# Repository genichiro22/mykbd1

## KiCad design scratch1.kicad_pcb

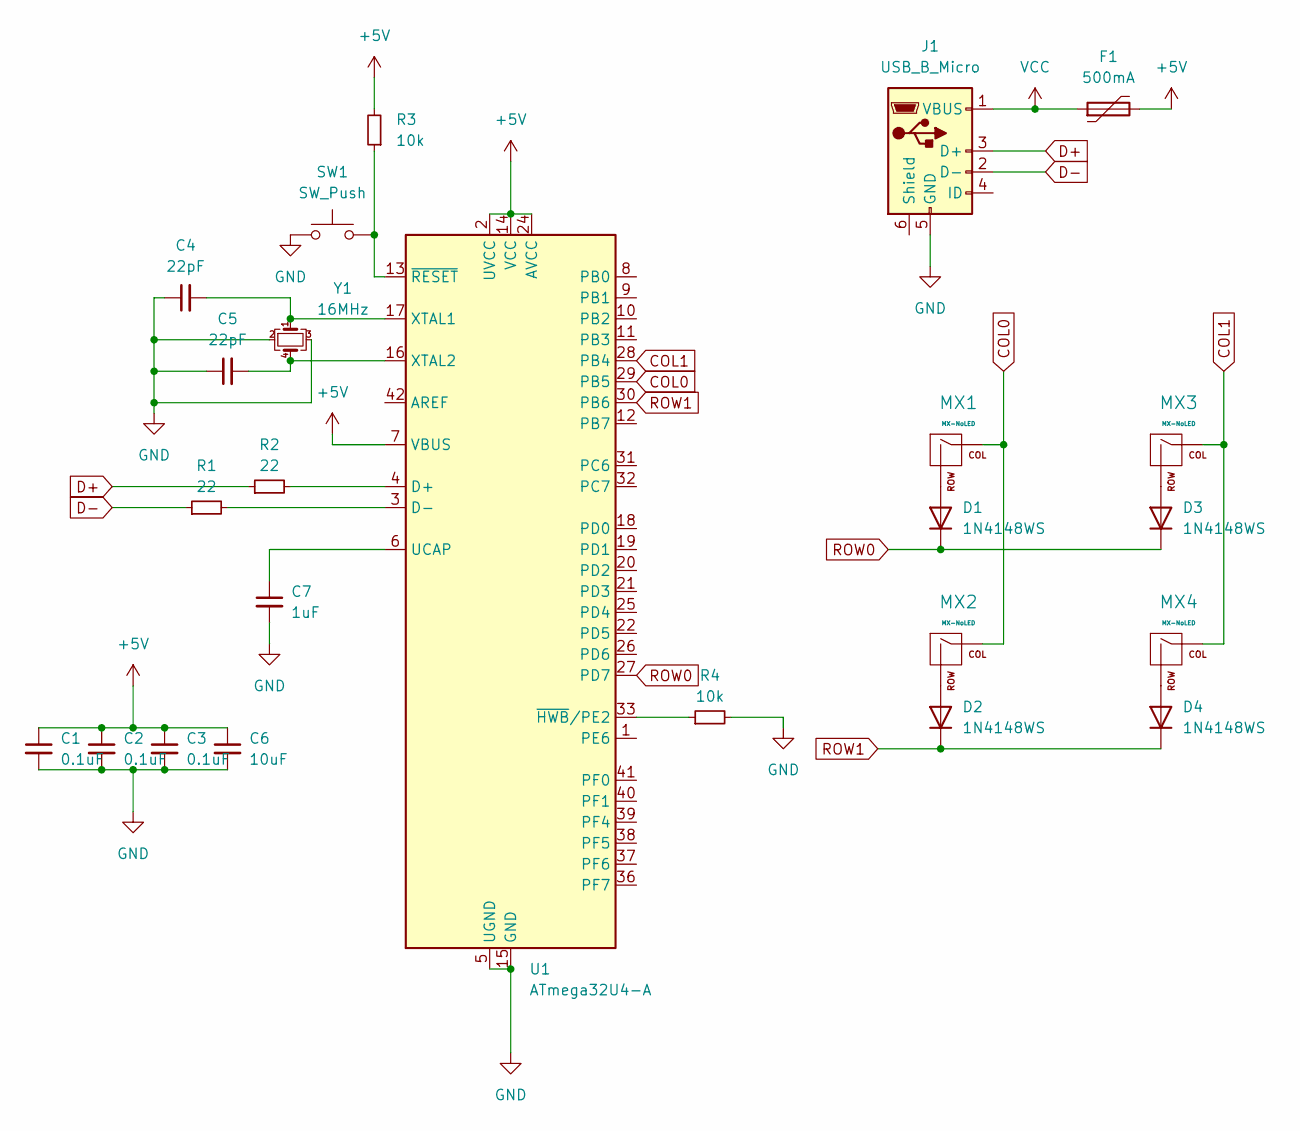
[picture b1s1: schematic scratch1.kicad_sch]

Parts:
C1, C2, C3: 0.1uF; C_0805_2012Metric
C4, C5: 22pF; C_0805_2012Metric
C6: 10uF; C_0805_2012Metric
C7: 1uF; C_0805_2012Metric
D1, D2, D3, D4: 1N4148WS; D_SOD-323
F1: 500mA; Fuse_1206_3216Metric
J1: USB_B_Micro; Molex-0548190589
MX1, MX2, MX3, MX4: MX-NoLED; MXOnly-1U-NoLED
R1, R2: 22; R_0805_2012Metric
R3, R4: 10k; R_0805_2012Metric
SW1: SW_Push; SKQG-1155865
U1: ATmega32U4-A; TQFP-44_10x10mm_P0.8mm
Y1: 16MHz; Crystal_SMD_3225-4Pin_3.2x2.5mm

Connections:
+5V: C1.1, C2.1, C3.1, C6.1, F1.2, R3.2, U1.2 (UVCC), U1.7 (VBUS), U1.14 (VCC), U1.24 (AVCC), U1.34 (VCC), U1.44 (AVCC)
COL0: MX1.1 (COL), MX2.1 (COL), U1.29 (PB5)
COL1: MX3.1 (COL), MX4.1 (COL), U1.28 (PB4)
D+: J1.3 (D+), R2.1
D-: J1.2 (D-), R1.1
GND: C1.2, C2.2, C3.2, C4.1, C5.1, C6.2, C7.2, J1.5 (GND), R4.2, SW1.1, U1.5 (UGND), U1.15 (GND), U1.23 (GND), U1.35 (GND), U1.43 (GND), Y1.2, Y1.3
unnamed: D1.2 (A), MX1.2 (ROW)
unnamed: D2.2 (A), MX2.2 (ROW)
unnamed: D3.2 (A), MX3.2 (ROW)
unnamed: D4.2 (A), MX4.2 (ROW)
unnamed: R2.2, U1.4 (D+)
unnamed: R1.2, U1.3 (D-)
unnamed: C7.1, U1.6 (UCAP)
unnamed: C4.2, U1.17 (XTAL1), Y1.1
unnamed: C5.2, U1.16 (XTAL2), Y1.4
unnamed: R4.1, U1.33 (~HWB/PE2)
unnamed: R3.1, SW1.2, U1.13 (~RESET)
ROW0: D1.1 (K), D3.1 (K), U1.27 (PD7)
ROW1: D2.1 (K), D4.1 (K), U1.30 (PB6)
VCC: F1.1, J1.1 (VBUS)

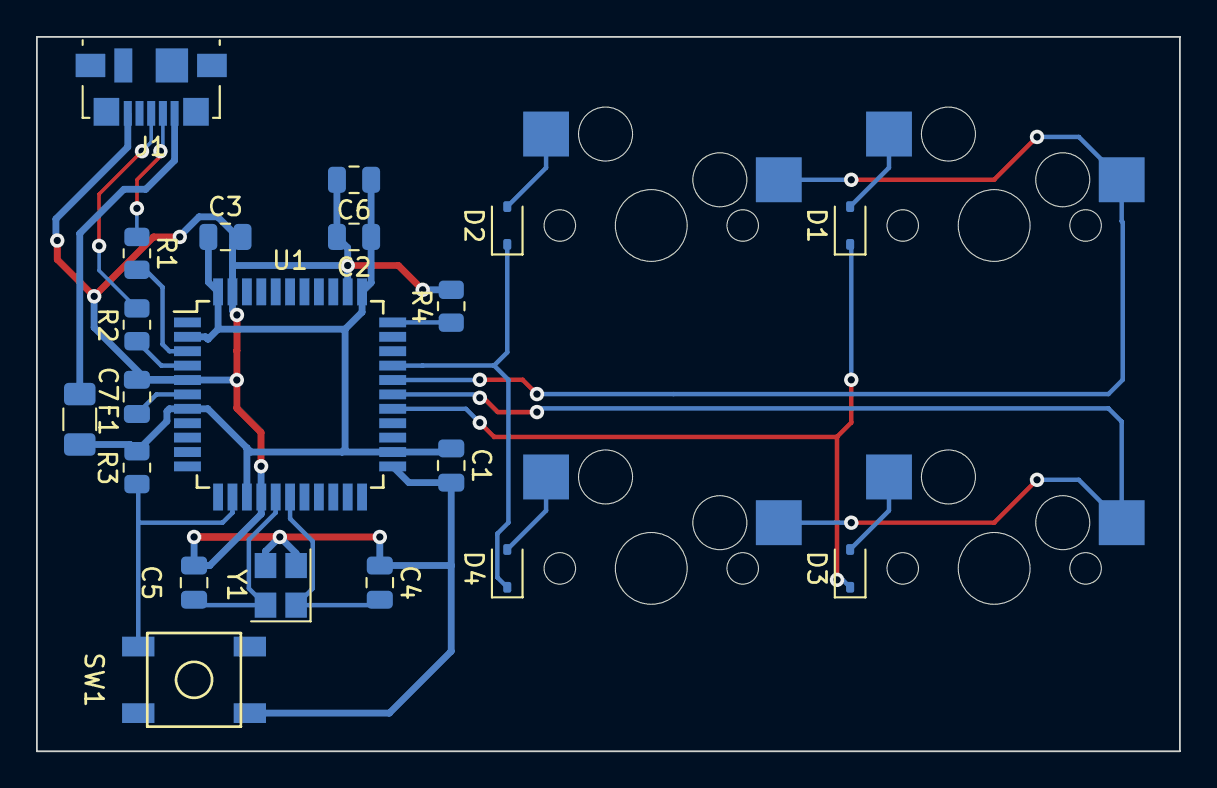
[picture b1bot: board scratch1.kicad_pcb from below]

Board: 2 copper layers, 63.5 x 39.7 mm, 24 parts (20 on the bottom side), 20 nets.

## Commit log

2023-09-12 add submodules
2023-09-12 add local libraries to kicad files
2023-09-13 atmega32u4 added
2023-09-14 complete MCU zone schema
2023-09-14 complete schema
2023-09-14 assined footprints
2023-09-14 place footprints
2023-09-14 finished routing
2023-09-14 connector updated, but MX footprint to be also updated
2023-09-15 error solved
